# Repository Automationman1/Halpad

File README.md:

# Halpad
Halpad is a 9 key macropad with a knob and OLED designed around the idea of quickly selecting features.

## Features:
- Simplistic case design
- 128x32 OLED Display
- EC11 Rotary encoder
- 9 Switches

## CAD Model:
For the case, only M3x16mm and M3 heatset inserts are used for hardware, allowing for a simple BOM. It also only uses 3 3d printed parts for assembly, allowing for a quick and straightforward build.

Made in Fusion

## PCB:
Screenshot of the Schematic:

Screenshot of the PCB:

Made in KiCad

## Firmware:
This macropad uses KMK firmware currently, with plans to use QMK in the future.

## BOM:

- 9x Cherry MX Switches
- 9x Keycaps (whatever profile, designed around standard spacing)
- 4x M3x5x4 Heatset Inserts
- 4x M3x16mm SHCS Bolts
- 10x 1N4148 DO-35 Diodes
- 1x 0.91" 128x32 OLED Display
- 1x EC11 Rotary Encoder
- 1x XIAO RP2040
- 1x Case (3 printed parts)

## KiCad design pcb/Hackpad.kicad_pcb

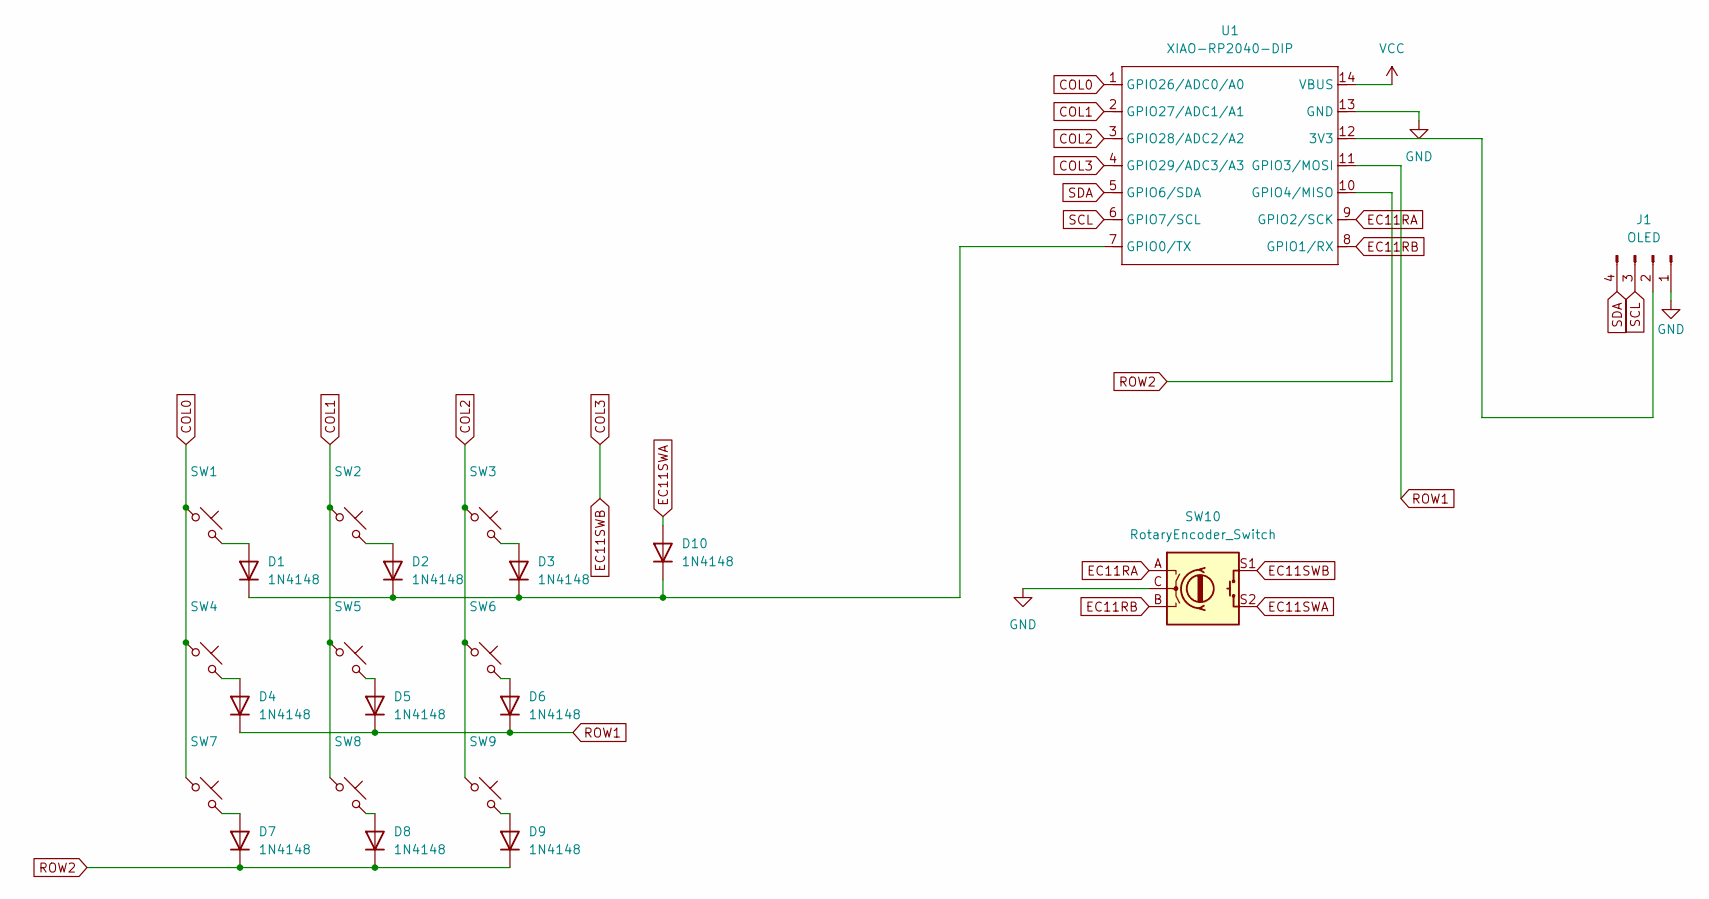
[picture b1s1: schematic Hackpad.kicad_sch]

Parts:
D1, D2, D3, D4, D5, D6, D7, D8, D9, D10: 1N4148; D_DO-35_SOD27_P7.62mm_Horizontal
J1: OLED; SSD1306-0.91-OLED-4pin-128x32
SW1, SW2, SW3, SW4, SW5, SW6, SW7, SW8, SW9: SW_Push_45deg; SW_Cherry_MX_1.00u_PCB
SW10: RotaryEncoder_Switch; RotaryEncoder_Alps_EC11E-Switch_Vertical_H20mm
U1: XIAO-RP2040-DIP

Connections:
COL0: SW1.1, SW4.1, SW7.1, U1.1 (GPIO26/ADC0/A0)
COL1: SW2.1, SW5.1, SW8.1, U1.2 (GPIO27/ADC1/A1)
COL2: SW3.1, SW6.1, SW9.1, U1.3 (GPIO28/ADC2/A2)
COL3: SW10.S1, U1.4 (GPIO29/ADC3/A3)
EC11RA: SW10.A, U1.9 (GPIO2/SCK)
EC11RB: SW10.B, U1.8 (GPIO1/RX)
EC11SWA: D10.2 (A), SW10.S2
GND: J1.1, SW10.C, U1.13 (GND)
unnamed: D1.2 (A), SW1.2
unnamed: D1.1 (K), D2.1 (K), D3.1 (K), D10.1 (K), U1.7 (GPIO0/TX)
unnamed: D2.2 (A), SW2.2
unnamed: D3.2 (A), SW3.2
unnamed: D4.2 (A), SW4.2
unnamed: D5.2 (A), SW5.2
unnamed: D6.2 (A), SW6.2
unnamed: D7.2 (A), SW7.2
unnamed: D8.2 (A), SW8.2
unnamed: D9.2 (A), SW9.2
unnamed: J1.2, U1.12 (3V3)
ROW1: D4.1 (K), D5.1 (K), D6.1 (K), U1.11 (GPIO3/MOSI)
ROW2: D7.1 (K), D8.1 (K), D9.1 (K), U1.10 (GPIO4/MISO)
SCL: J1.3, U1.6 (GPIO7/SCL)
SDA: J1.4, U1.5 (GPIO6/SDA)
VCC: U1.14 (VBUS)

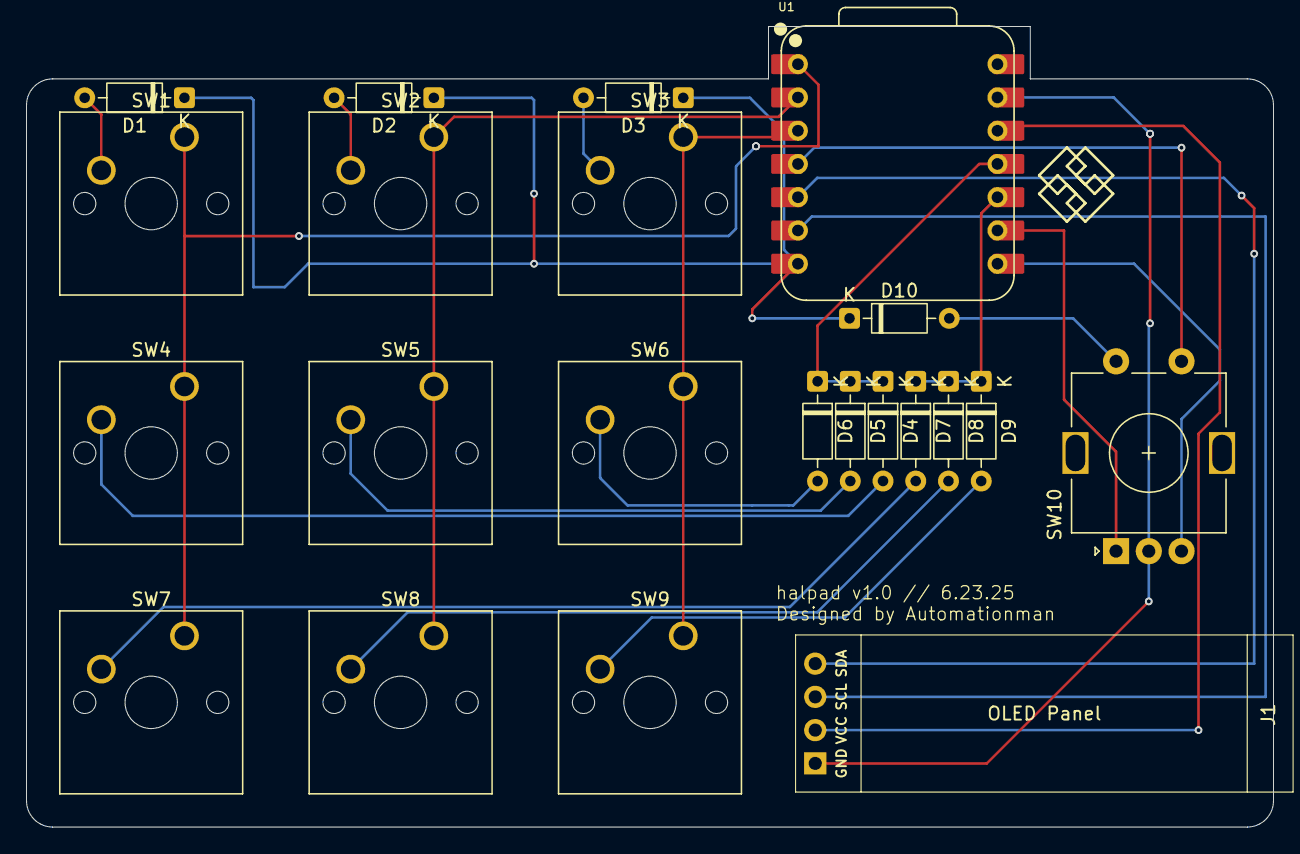
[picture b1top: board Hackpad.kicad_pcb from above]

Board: 2 copper layers, 95.2 x 61.1 mm, 22 parts (0 on the bottom side), 23 nets.

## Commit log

2025-06-26 Create halpad
2025-06-26 Create python
2025-06-26 Create pcb
2025-06-26 Create production
